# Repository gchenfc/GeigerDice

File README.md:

# GeigerDice
Produce random dice rolls using a Geiger Counter as the randomness source for QRNG "true random numbers"

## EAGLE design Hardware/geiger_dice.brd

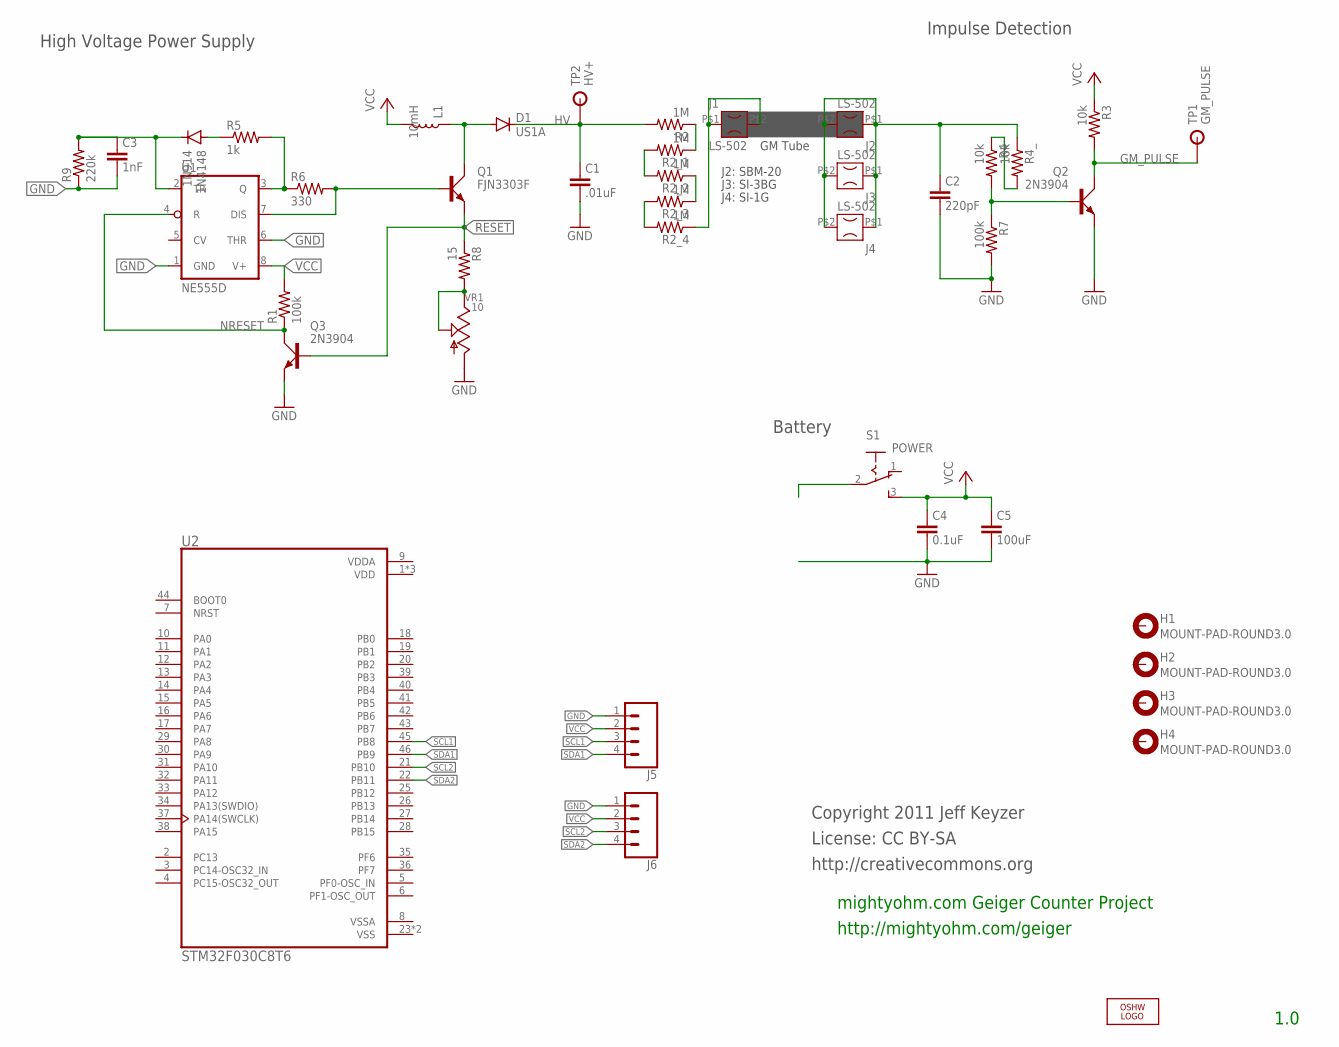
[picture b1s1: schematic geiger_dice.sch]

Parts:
1N4148: 1N914; SOD123
C1: .01uF; CAP_0805
C2: 220pF; CAP_1206
C3: 1nF; CAP_0805
C4: 0.1uF; CAP_0805
C5: 100uF; CAP_1206
D1: US1A; DO214AC
H1, H2, H3, H4: MOUNT-PAD-ROUND3.0; 3,0-PAD
J1, J2, J3, J4: LS-502
J5, J6: CONN_04; 1X04
L1: 10mH; VLU0608
LOGO1: OSHW_LOGO_FILLX0200-NT; OSHW_FILLX200_NOTEXT
Q1: FJN3303F; TO92C
Q2, Q3: 2N3904; TO92D
R1: 100k; 0805
R2, R2_1, R2_2, R2_3, R2_4: 1M; 1206
R3: 10k; 0805
R4, R4_: 10k; 1206
R5: 1k; 0805
R6: 330; 0805
R7: 100k; 1206
R8: 15; 0805
R9: 220k; 0805
S1: POWER; OS102011
TP1: GM_PULSE; TP_PTH
TP2: HV+; TP_PTH
U1: NE555D; SO08
U2: STM32F030C8T6; QFP50P900X900X160-48N
VR1: 10; 3314J-1

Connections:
GM_PULSE: Q2.C, R3.2, TP1.P$1
GND: C1.2, C2.2, C3.2, C4.2, C5.2, J5.1, J6.1, Q2.E, Q3.E, R7.2, R9.1, U1.1 (GND), U1.6 (THR), VR1.3
HV: C1.1, D1.C, R2.2, TP2.P$1
unnamed: 1N4148.A, R5.1
unnamed: R4.1, R4_.2
unnamed: Q1.B, R6.2, U1.7 (DIS)
unnamed: 1N4148.C, C3.1, R9.2, U1.2 (TR)
unnamed: R5.2, R6.1, U1.3 (Q)
unnamed: R2_3.2, R2_4.2
unnamed: D1.A, L1.P$1 (1), Q1.C
unnamed: Q2.B, R4.2, R7.1
unnamed: J1.P$1 (1), J1.P$2 (2), R2_4.1
unnamed: R8.2, VR1.1, VR1.2
unnamed: R2.1, R2_1.1
unnamed: R2_1.2, R2_2.2
unnamed: R2_2.1, R2_3.1
unnamed: C2.1, J2.P$1 (1), J2.P$2 (2), J3.P$1 (1), J3.P$2 (2), J4.P$1 (1), J4.P$2 (2), R4_.1
NRESET: Q3.C, R1.1, U1.4 (R)
RESET: Q1.E, Q3.B, R8.1
SCL1: J5.3, U2.45 (PB8)
SCL2: J6.3, U2.21 (PB10)
SDA1: J5.4, U2.46 (PB9)
SDA2: J6.4, U2.22 (PB11)
VCC: C4.1, C5.1, J5.2, J6.2, L1.P$2 (2), R1.2, R3.1, S1.3, U1.8 (V+)
VDD: U2.1 (VDD), U2.24 (VDD), U2.48 (VDD)
VDDA: U2.9 (VDDA)
VSS: U2.23 (VSS), U2.47 (VSS)
VSSA: U2.8 (VSSA)

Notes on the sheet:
1.0
mightyohm.com Geiger Counter Project
GM Tube
License: CC BY-SA
http://creativecommons.org
http://mightyohm.com/geiger
Copyright 2011 Jeff Keyzer
J2: SBM-20
J3: SI-3BG
J4: SI-1G
High Voltage Power Supply
Impulse Detection
Battery

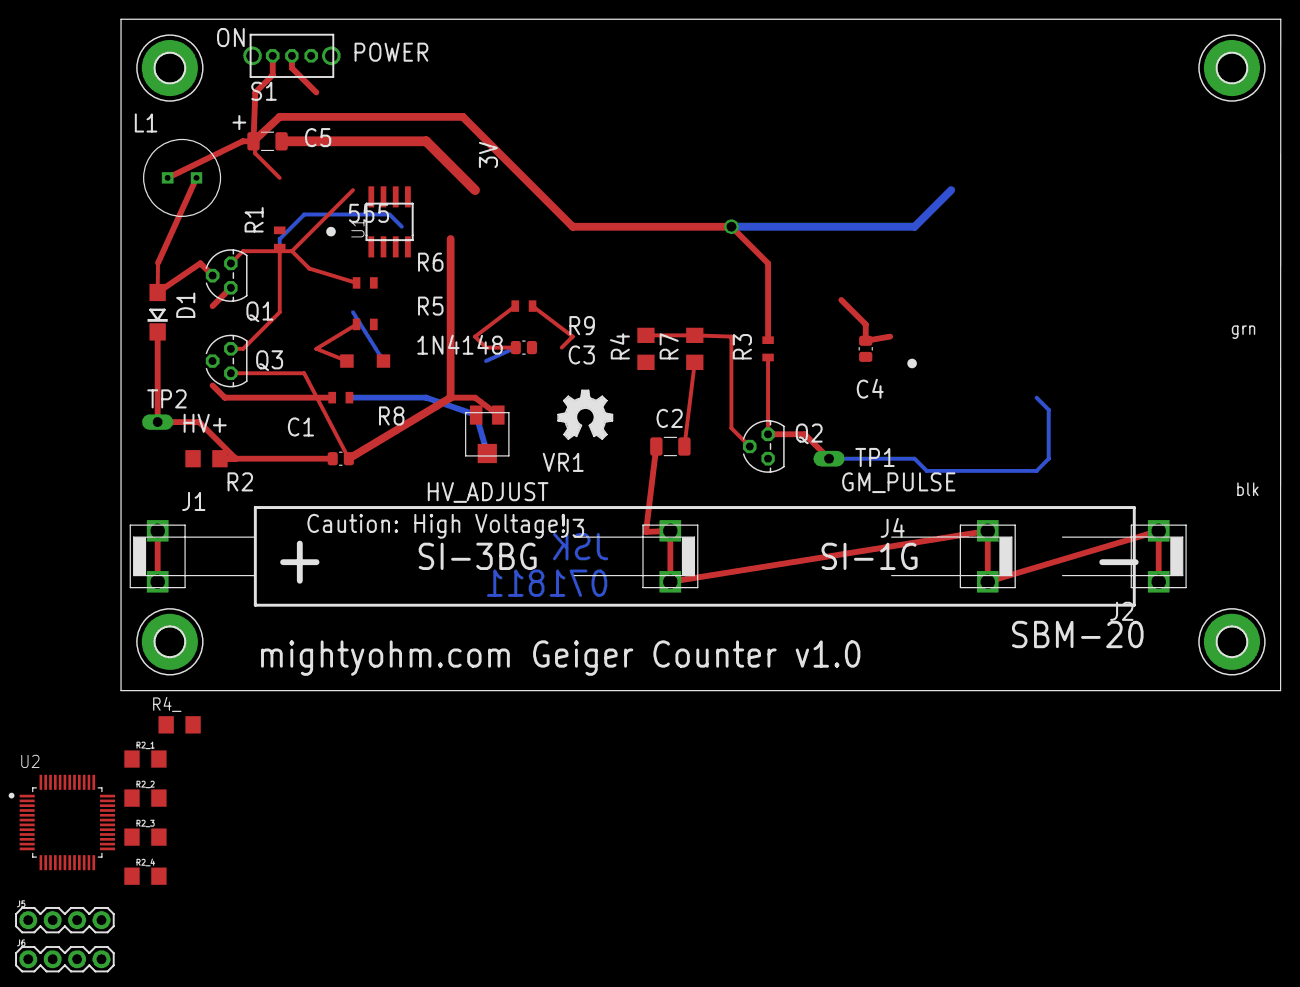
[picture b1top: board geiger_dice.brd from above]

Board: 2 copper layers, 120.7 x 69.8 mm, 42 parts (0 on the bottom side), 26 nets.

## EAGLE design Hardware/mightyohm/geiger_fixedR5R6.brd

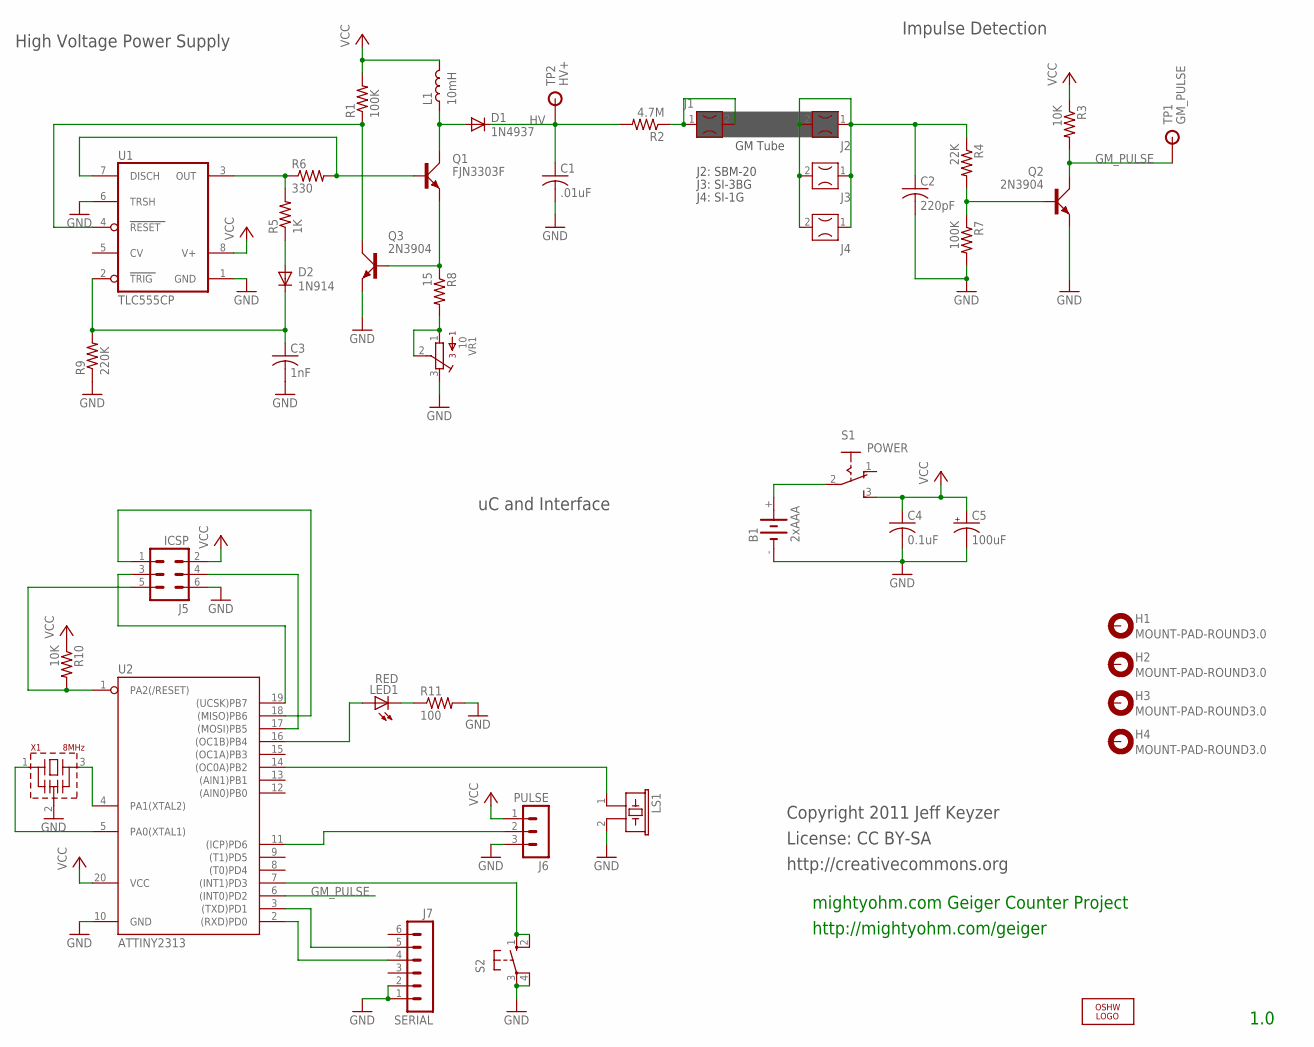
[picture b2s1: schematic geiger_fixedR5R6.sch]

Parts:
B1: 2xAAA; 12BH423-GR
C1: .01uF; C102-043X133
C2: 220pF; C050-030X075
C3: 1nF; C050-025X075
C4: 0.1uF; C025-025X050
C5: 100uF; E2,5-6
D1: 1N4937; DO41-10
D2: 1N914; DO35-7
H1, H2, H3, H4: MOUNT-PAD-ROUND3.0; 3,0-PAD
J1, J2, J3, J4: FUSECLIPPCMOUNT; FUSECLIP_PCMOUNT
J5: ICSP; ICSP-6
J6: PULSE; MA03-1
J7: SERIAL; MA06-1
L1: 10mH; ELC09D
LED1: RED; LED5MM
LOGO1: OSHW_LOGO_FILLX0200-NT; OSHW_FILLX200_NOTEXT
LS1: PIEZO17MM; PS1740P02E
Q1: FJN3303F; TO92C
Q2, Q3: 2N3904; TO92D
R1, R7: 100K; 0207/10
R2: 4.7M; 0207/10
R3, R10: 10K; 0207/10
R4: 22K; 0207/10
R5: 1K; 0207/10
R6: 330; 0207/10
R8: 15; 0207/10
R9: 220K; 0207/10
R11: 100; 0207/10
S1: POWER; OS102011
S2: 10-XX; B3F-10XX
TP1: GM_PULSE; TP_PTH
TP2: HV+; TP_PTH
U1: TLC555CP; DIL08
U2: ATTINY2313; DIL20
VR1: 10; 3386P
X1: 8MHz; CSTLA_T

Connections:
GM_PULSE: Q2.C, R3.2, TP1.P$1, U2.6 ((INT0)PD2)
GND: B1.-, C1.2, C2.2, C3.2, C4.2, C5.-, J5.6, J6.3, J7.1, J7.2, LS1.2, Q2.E, Q3.E, R7.2, R9.1, R11.2, S2.3, S2.4 (P1), U1.1 (GND), U1.6 (TRSH), U2.10 (GND), VR1.3, X1.2 (VSS)
HV: C1.1, D1.C, R2.2, TP2.P$1
unnamed: D2.A, R5.1
unnamed: S2.1 (S), S2.2 (S1), U2.7 ((INT1)PD3)
unnamed: Q3.C, R1.1, U1.4 (RESET)
unnamed: LS1.1, U2.14 ((OC0A)PB2)
unnamed: B1.+, S1.2
unnamed: J5.4, U2.17 ((MOSI)PB5)
unnamed: J5.3, U2.19 ((UCSK)PB7)
unnamed: Q1.B, R6.2, U1.7 (DISCH)
unnamed: C3.1, D2.C, R9.2, U1.2 (TRIG)
unnamed: R5.2, R6.1, U1.3 (OUT)
unnamed: Q1.E, Q3.B, R8.1
unnamed: D1.A, L1.1, Q1.C
unnamed: J5.5, R10.2, U2.1 (PA2(/RESET))
unnamed: Q2.B, R4.2, R7.1
unnamed: J1.1, J1.2, R2.1
unnamed: J7.4, U2.2 ((RXD)PD0)
unnamed: J7.5, U2.3 ((TXD)PD1)
unnamed: U2.4 (PA1(XTAL2)), X1.3
unnamed: U2.5 (PA0(XTAL1)), X1.1
unnamed: J6.2, U2.11 ((ICP)PD6)
unnamed: LED1.K (C), R11.1
unnamed: LED1.A, U2.16 ((OC1B)PB4)
unnamed: R8.2, VR1.1, VR1.2
unnamed: C2.1, J2.1, J2.2, J3.1, J3.2, J4.1, J4.2, R4.1
unnamed: J5.1, U2.18 ((MISO)PB6)
VCC: C4.1, C5.+, J5.2, J6.1, L1.2, R1.2, R3.1, R10.1, S1.3, U1.8 (V+), U2.20 (VCC)

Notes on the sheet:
1.0
mightyohm.com Geiger Counter Project
GM Tube
License: CC BY-SA
http://creativecommons.org
http://mightyohm.com/geiger
Copyright 2011 Jeff Keyzer
J2: SBM-20
J3: SI-3BG
J4: SI-1G
High Voltage Power Supply
Impulse Detection
uC and Interface

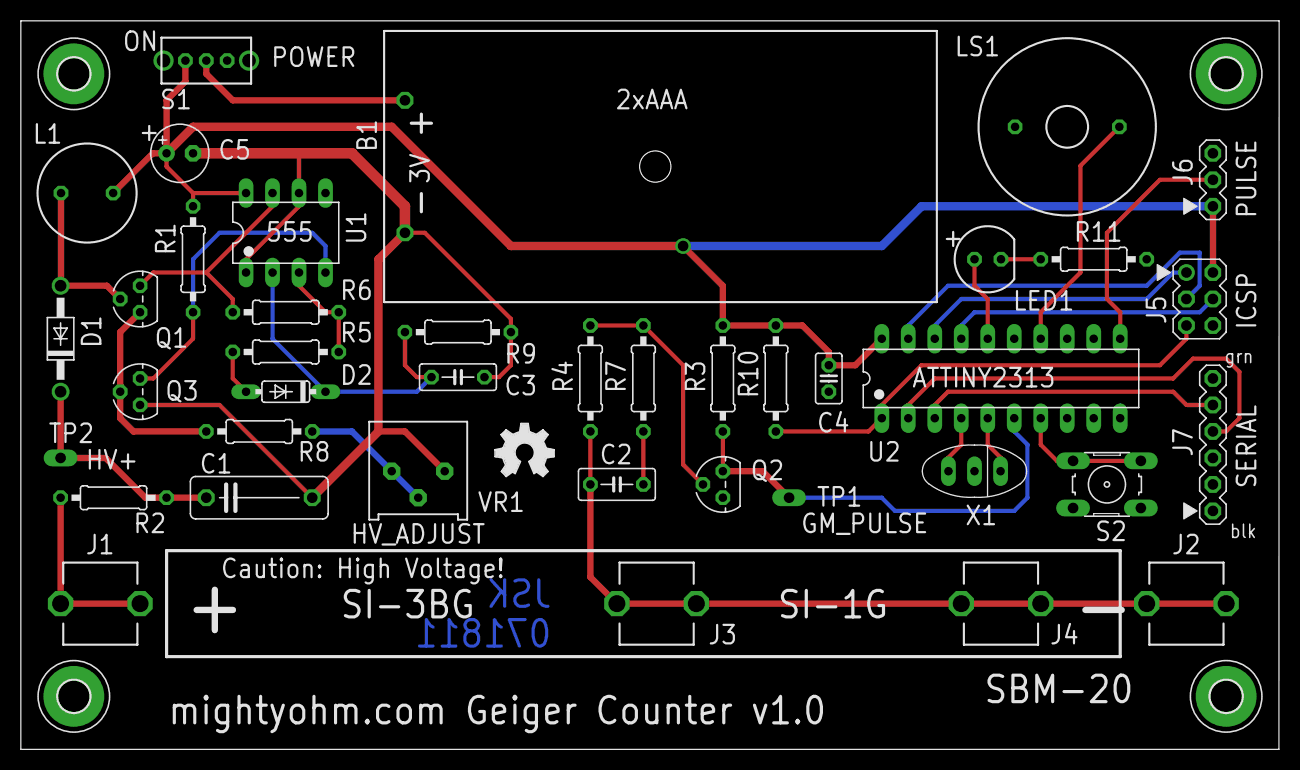
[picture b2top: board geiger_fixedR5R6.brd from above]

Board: 2 copper layers, 120.7 x 69.8 mm, 45 parts (0 on the bottom side), 29 nets.

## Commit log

2022-07-15 Reference from https://mightyohm.com/blog/products/geiger-counter/design-files/
2022-07-18 progress from July 15, together with JD

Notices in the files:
parts and their libraries:
SparkFun-Connectors: Licensing: Creative Commons ShareAlike 4.0 International - https://creativecommons.org/licenses/by-sa/4.0
